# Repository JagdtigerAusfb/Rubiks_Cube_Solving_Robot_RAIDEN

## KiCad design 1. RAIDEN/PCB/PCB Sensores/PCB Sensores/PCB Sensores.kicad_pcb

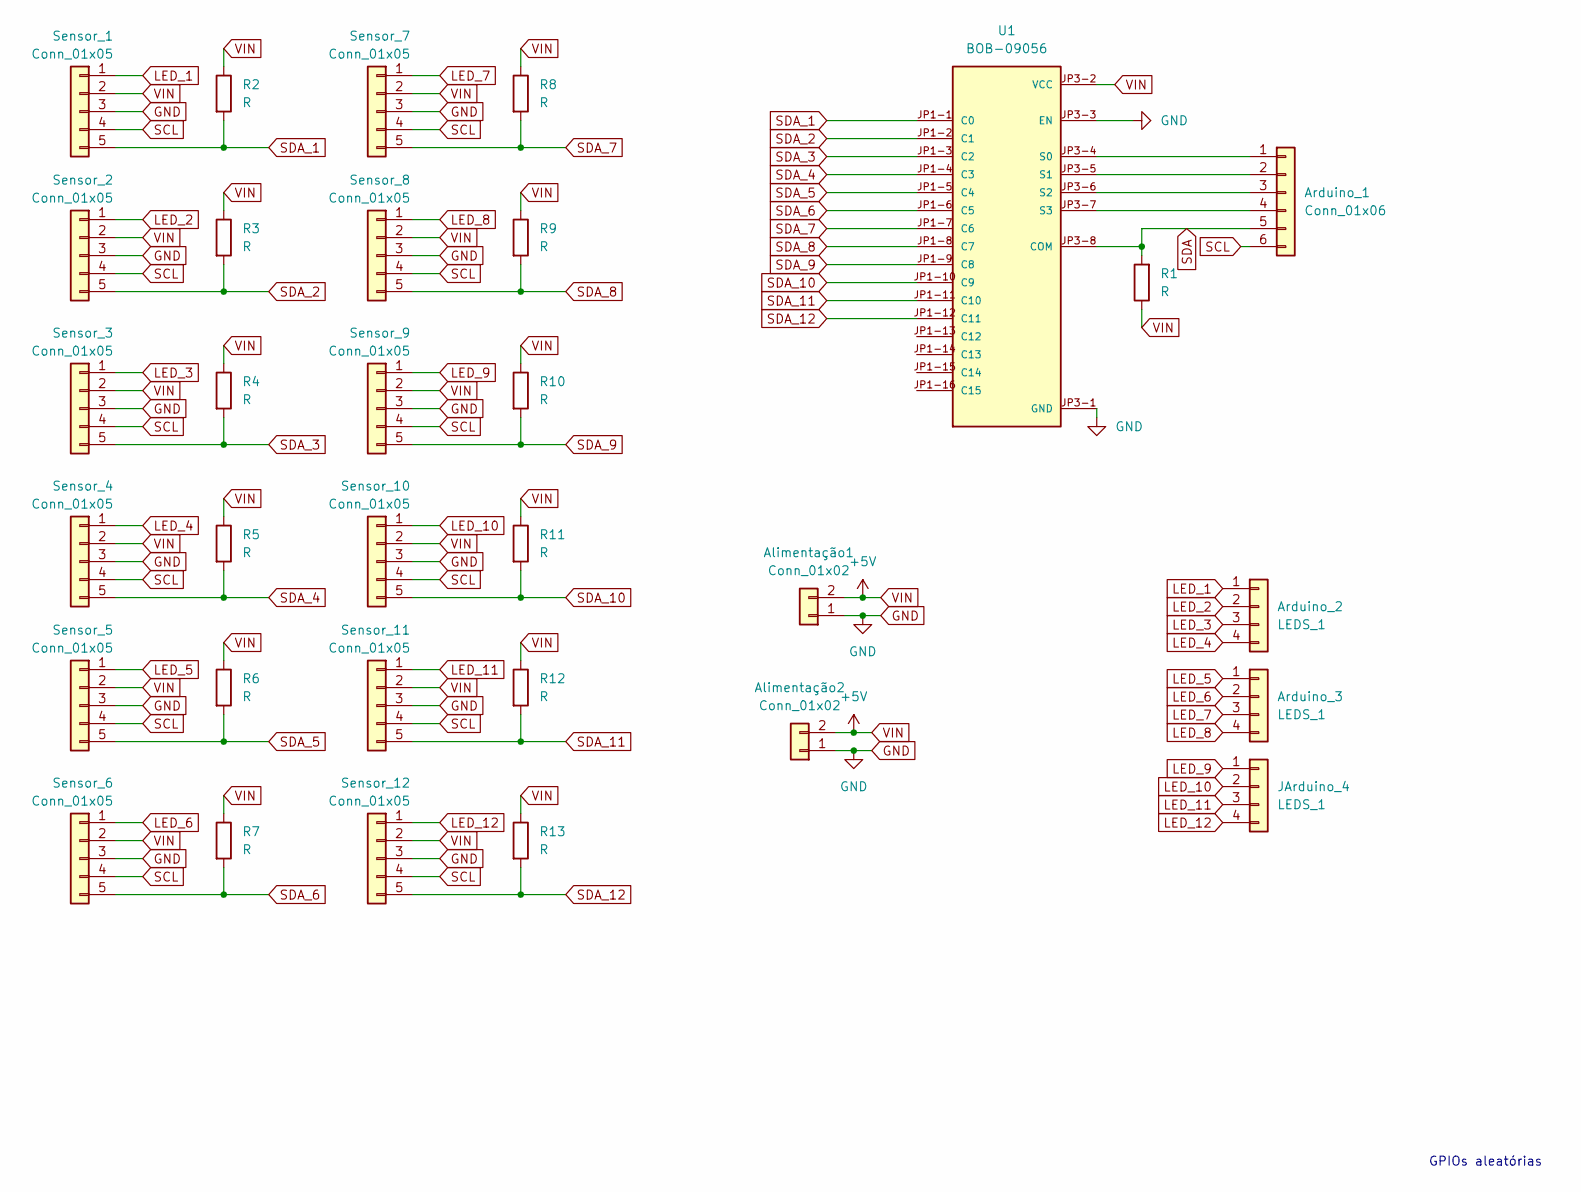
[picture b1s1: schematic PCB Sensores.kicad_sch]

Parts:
Alimentação1, Alimentação2: Conn_01x02; PinSocket_1x02_P2.54mm_Vertical
Arduino_1: Conn_01x06; PinHeader_1x06_P2.54mm_Vertical
Arduino_2, Arduino_3: LEDS_1; PinSocket_1x04_P2.54mm_Vertical
JArduino_4: LEDS_1; PinSocket_1x04_P2.54mm_Vertical
R1, R2, R3, R4, R5, R6, R7, R8, R9, R10, R11, R12, R13: R; R_Axial_DIN0207_L6.3mm_D2.5mm_P7.62mm_Horizontal
Sensor_1, Sensor_2, Sensor_3, Sensor_4, Sensor_5, Sensor_6, Sensor_7, Sensor_8, Sensor_9, Sensor_10, Sensor_11, Sensor_12: Conn_01x05; PinSocket_1x05_P2.54mm_Vertical
U1: BOB-09056; MODULE_BOB-09056; PARTREV v11

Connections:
GND: Alimentação1.1, Alimentação2.1, Sensor_1.3, Sensor_2.3, Sensor_3.3, Sensor_4.3, Sensor_5.3, Sensor_6.3, Sensor_7.3, Sensor_8.3, Sensor_9.3, Sensor_10.3, Sensor_11.3, Sensor_12.3, U1.JP3-1 (GND), U1.JP3-3 (EN)
LED_1: Arduino_2.1, Sensor_1.1
LED_2: Arduino_2.2, Sensor_2.1
LED_3: Arduino_2.3, Sensor_3.1
LED_4: Arduino_2.4, Sensor_4.1
LED_5: Arduino_3.1, Sensor_5.1
LED_6: Arduino_3.2, Sensor_6.1
LED_7: Arduino_3.3, Sensor_7.1
LED_8: Arduino_3.4, Sensor_8.1
LED_9: JArduino_4.1, Sensor_9.1
LED_10: JArduino_4.2, Sensor_10.1
LED_11: JArduino_4.3, Sensor_11.1
LED_12: JArduino_4.4, Sensor_12.1
unnamed: Arduino_1.1, U1.JP3-4 (S0)
unnamed: Arduino_1.2, U1.JP3-5 (S1)
unnamed: Arduino_1.3, U1.JP3-6 (S2)
unnamed: Arduino_1.4, U1.JP3-7 (S3)
SCL: Arduino_1.6, Sensor_1.4, Sensor_2.4, Sensor_3.4, Sensor_4.4, Sensor_5.4, Sensor_6.4, Sensor_7.4, Sensor_8.4, Sensor_9.4, Sensor_10.4, Sensor_11.4, Sensor_12.4
SDA: Arduino_1.5, R1.2, U1.JP3-8 (COM)
SDA_1: R2.2, Sensor_1.5, U1.JP1-1 (C0)
SDA_2: R3.2, Sensor_2.5, U1.JP1-2 (C1)
SDA_3: R4.2, Sensor_3.5, U1.JP1-3 (C2)
SDA_4: R5.2, Sensor_4.5, U1.JP1-4 (C3)
SDA_5: R6.2, Sensor_5.5, U1.JP1-5 (C4)
SDA_6: R7.2, Sensor_6.5, U1.JP1-6 (C5)
SDA_7: R8.2, Sensor_7.5, U1.JP1-7 (C6)
SDA_8: R9.2, Sensor_8.5, U1.JP1-8 (C7)
SDA_9: R10.2, Sensor_9.5, U1.JP1-9 (C8)
SDA_10: R11.2, Sensor_10.5, U1.JP1-10 (C9)
SDA_11: R12.2, Sensor_11.5, U1.JP1-11 (C10)
SDA_12: R13.2, Sensor_12.5, U1.JP1-12 (C11)
VIN: Alimentação1.2, Alimentação2.2, R1.1, R2.1, R3.1, R4.1, R5.1, R6.1, R7.1, R8.1, R9.1, R10.1, R11.1, R12.1, R13.1, Sensor_1.2, Sensor_2.2, Sensor_3.2, Sensor_4.2, Sensor_5.2, Sensor_6.2, Sensor_7.2, Sensor_8.2, Sensor_9.2, Sensor_10.2, Sensor_11.2, Sensor_12.2, U1.JP3-2 (VCC)

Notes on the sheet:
GPIOs aleatórias

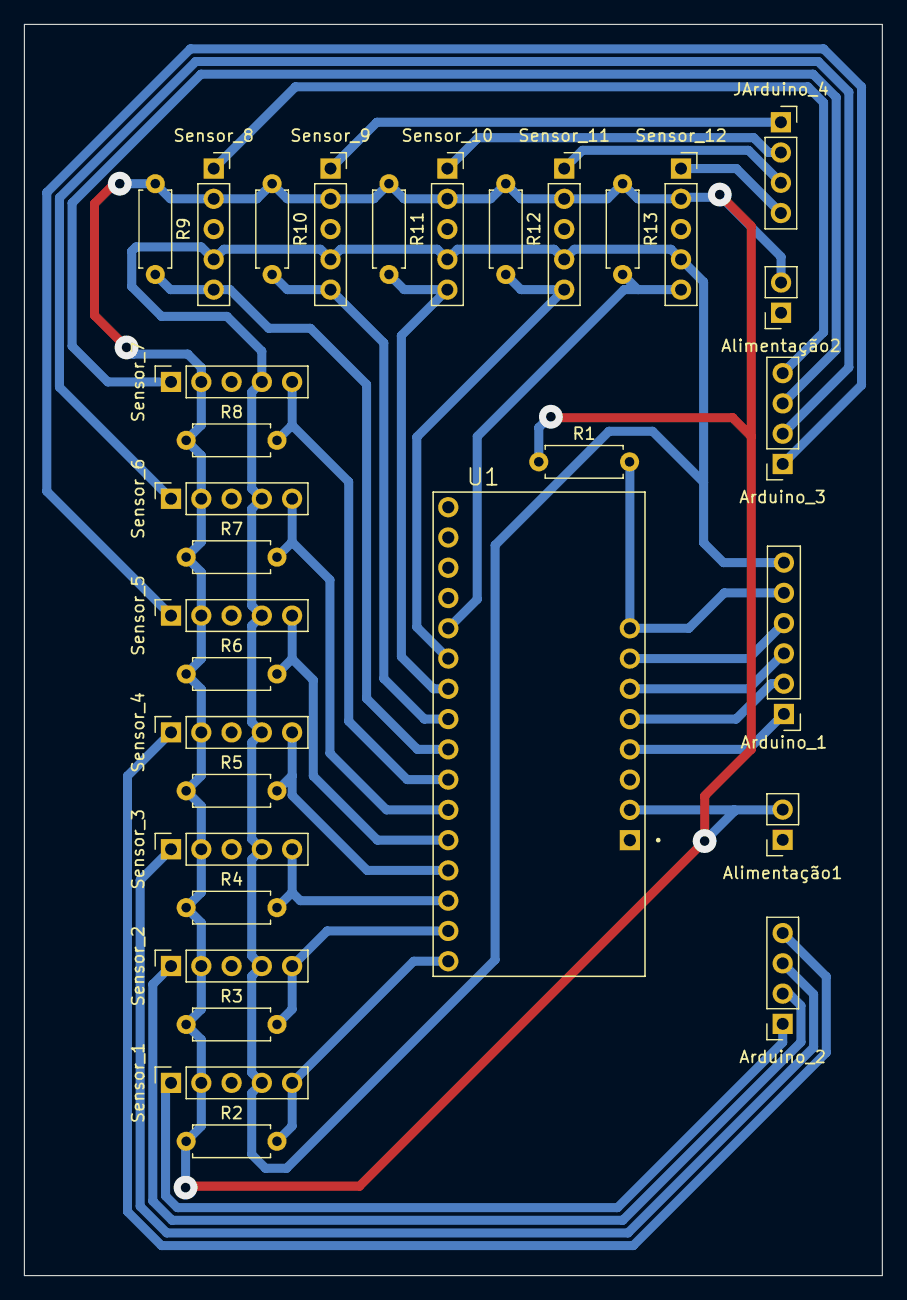
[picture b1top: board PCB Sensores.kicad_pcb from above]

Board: 2 copper layers, 72.0 x 105.0 mm, 32 parts (0 on the bottom side), 32 nets.
